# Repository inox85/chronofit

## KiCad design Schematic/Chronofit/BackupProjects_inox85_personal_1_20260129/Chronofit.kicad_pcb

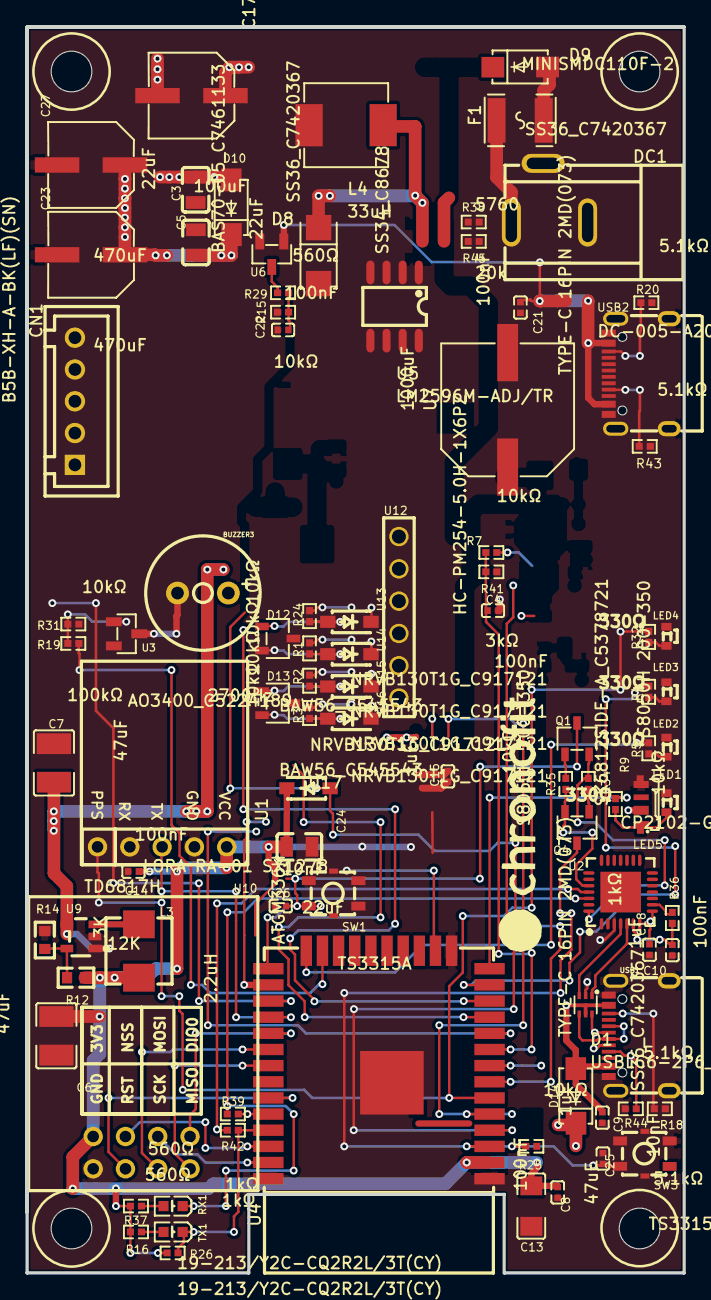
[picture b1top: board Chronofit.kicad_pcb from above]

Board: 4 copper layers, 51.7 x 98.0 mm, 96 parts (0 on the bottom side), 63 nets.

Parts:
BUZZER3: 2700Hz; BUZ-TH_BD9.0-P4.00-D0.6-FD
C3, C5, C24: 22uF; C0805
C4, C8, C14, C18, C21, C22: 100nF; C0402
C6, C7: 47uF; C1210
C9, C10, C15: 1uF; C0402
C13: 47uF; C1206
C17: 100uF; CAP-SMD_BD6.3-L6.6-W6.6-LS7.6-FD
C23, C27: 470uF; CAP-SMD_BD6.3-L6.6-W6.6-LS7.6-RD
C25, C26: 10nF; C0402
CN1: B5B-XH-A-BK(LF)(SN); CONN-TH_B5B-XH-A-BK-LF-SN
D1: USBLC6-2P6_C49451919; SOT-563_L1.6-W1.2-P0.50-LS1.6-BL
D8: SS34_C8678; SMA_L4.3-W2.6-LS5.2-RD
D9, D10, D14: SS36_C7420367; SMA_L4.3-W2.6-LS5.0-FD
D12, D13: BAW56_C545543; SOT-23-3_L2.9-W1.6-P1.90-LS2.8-BR
DC1: DC-005-A200; DC-IN-TH_DC-005-A200
F1: MINISMDC110F-2; F1812
Hole_gge181386: Hole_gge181386
Hole_gge189325: Hole_gge189325
Hole_gge196727: Hole_gge196727
Hole_gge200780: Hole_gge200780
L3: 2.2uH; IND-SMD_L5.2-W5.1
L4: 33uH; IND-SMD_L7.1-W6.6
LED1: BLUE_LED; LED-SMD_L1.7-W1.1-R-RD_GREEN
LED2: RED_LED; LED-SMD_L1.7-W1.1-R-RD_GREEN
LED3: GREEN_LED; LED-SMD_L1.7-W1.1-R-RD_GREEN
LED4: ORANGE_LED; LED-SMD_L1.7-W1.1-R-RD_GREEN
LED5: SK6812SIDE-A_C5378721; LED-SMD_4P-L4.0-W1.6-L
Q1, Q4: S8050H 200-350; SOT-23-3_L2.9-W1.6-P1.90-LS2.8-BR
R1, R2, R3, R7, R19, R24, R25, R26, R29, R34, R35: 10kΩ; R0402
R4, R5, R9, R32: 330Ω; R0402
R12: 12K; R0603
R14: 3K; R0603
R15, R16, R37: 560Ω; R0402
R18, R20, R43, R44: 5.1kΩ; R0402
R31: 100kΩ; R0402
R36, R39, R42: 1kΩ; R0402
R38: 20k; R0402
R41: 3kΩ; R0402
R45: 5760; R0402
RX1: 19-213/Y2C-CQ2R2L/3T(CY); LED0603-R-RD
SW1, SW3: TS3315A; SW-SMD_4P-L3.4-W3.4-P2.00-LS4.0_TS3315A160GF
TX1: 19-213/Y2C-CQ2R2L/3T(CY); LED0603-R-RD
U1: ATGM336H
U2: CP2102-GMR; WQFN-28_L5.0-W5.0-P0.50-BL-EP3.2
U3: AO3400_C5224189; SOT-23-3_L2.9-W1.3-P0.95-LS2.4-BR
U4: ESP32-WROOM-32(8MB); WIFIM-SMD_39P-L25.5-W18.0-P1.27
U5: LM2596M-ADJ/TR; SOP-8_L4.9-W3.9-P1.27-LS6.0-BL
U6: BAS70-05_C7461133; SOT-23-3_L2.9-W1.3-P1.90-LS2.4-BR
U7: 1000uF; CAP-SMD_BD10.0-L10.3-W10.3-LS11.3-FD
U9: TD6817H; SOT-23-5_L2.9-W1.6-P0.95-LS2.8-BR
U10: LORA RA-01 SX1278
U12: HC-PM254-5.0H-1X6PZ; HDR-TH_HC-PM254-5.0H-1X6PZ
U13, U14, U15, U16, U17: NRVB130T1G_C917121; SOD-123_L2.7-W1.6-LS3.7-RD-1
USB1, USB2: TYPE-C 16PIN 2MD(073); USB-C-SMD_TYPE-C-6PIN-2MD-073

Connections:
+3V3: C6.2, C8.2, C13.1, C14.2, C24.2, L3.2, R1.2, R2.2, R3.2, R12.2, R16.1, R24.2, R25.2, R26.2, R37.1, U1.5, U4.2, U10.5, U17.1
+5V: BUZZER3.1, C5.2, C7.2, C15.2, C18.1, C21.2, C23.1, C27.1, CN1.1, D10.2, D14.2, LED5.2, R7.2, U2.7, U2.8, U6.1, U7.1, U9.1, U9.4, USB2.2, USB2.11
+5_EXT_BATT: C3.2, D10.1, L4.2, R38.2
+12V: C17.1, D9.2, U5.1, U6.2, U12.1
BATT_CHK: C4.2, R7.1, R41.2, U4.9
BUZZER: R19.2, U4.23
CE_SDA: U4.33, U10.2
CSN_SCL: U4.36, U10.6
D8_1: D8.1, L4.1, U5.2
D9_1: D9.1, F1.2
D+: D1.4, USB1.6, USB1.8
D+_OUT: D1.3, U2.4
D-: D1.6, USB1.5, USB1.7
D-_OUT: D1.1, U2.5
DC1_1: DC1.1, F1.1
DIO: U4.29, U10.8
DTR: Q1.2, R34.1, U2.28
EN: C25.2, Q4.3, R25.1, SW3.2, U4.3
GND: C3.1, C4.1, C5.1, C6.1, C7.1, C8.1, C9.1, C10.1, C13.2, C14.1, C15.1, C17.2, C18.2, C21.1, C22.1, C23.2, C24.1, C25.1, C26.1, C27.2, CN1.5, D1.2, D8.2, D12.3, D13.3, DC1.2, LED1.2, LED2.2, LED3.2, LED4.2, LED5.4, R14.1, R15.1, R18.1, R20.2, R31.1, R41.1, R43.2, R44.1, R45.1, SW1.3, SW1.4, SW1.5, SW3.3, SW3.4, SW3.5, U1.4, U2.3, U3.2, U4.1, U4.15, U4.38, U4.39, U5.3, U5.5, U7.2, U9.2, U10.1, U12.6, USB1.1, USB1.12, USB1.13, USB1.14, USB2.1, USB2.12, USB2.13, USB2.14
GPIO0: C26.2, D13.2, Q1.3, R3.1, SW1.2, U4.16, U4.25, U16.2
IN1: D12.1, R24.1, U4.11, U13.2
IN2: D12.2, R1.1, U4.12, U14.2
IN3: D13.1, R2.1, U4.10, U15.2
L3_1: L3.1, U9.3
LED1: R9.2, U4.14
LED2: R5.2, U4.24
LED2_1: LED2.1, R5.1
LED3: R4.2, U4.13
LED3_1: LED3.1, R4.1
LED4_1: LED4.1, R32.1
MISO: U4.31, U10.4
MOSI: U4.37, U10.7
POWER_CHK: C22.2, R15.2, R29.1, U4.4, U17.2
PPS_GPS: R32.2, U1.1, U4.6
Q1_1: Q1.1, R35.2
Q4_1: Q4.1, R34.2
R12_1: R12.1, R14.2, U9.5
R29_2: R29.2, U6.3
R38_1: R38.1, R45.2, U5.4
RGB_LED: LED1.1, LED5.1, R9.1
RTS: Q4.2, R35.1, U2.24
RX0: R39.1, U4.34
RX1_1: R37.2, RX1.1
RX1_2: R39.2, RX1.2, U2.26
RX_GPS: U1.3, U4.28
SCK: U4.30, U10.3
TX0: R26.1, R42.1, TX1.2, U4.35
TX1_1: R16.2, TX1.1
TX_PRINTER: CN1.4, U4.27
U2_6: C10.2, R36.1, U2.6
U2_9: R36.2, U2.9
U2_25: R42.2, U2.25
U3_1: R19.1, R31.2, U3.1
U3_3: BUZZER3.2, U3.3
U12_2: U12.2, U13.1
U12_3: U12.3, U14.1
U12_4: U12.4, U15.1
U12_5: U12.5, U16.1
USB1_4: R44.2, USB1.4
USB1_10: R18.2, USB1.10
USB2_4: R43.1, USB2.4
USB2_10: R20.1, USB2.10
VBUS: C9.2, D1.5, D14.1, USB1.2, USB1.11

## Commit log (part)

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2026-01-02 Creazione nuovo progetto pulito
2026-01-03 Varie implementazioni
2026-01-03 Risoluzione problemi di sincro
2026-01-04 Revert "Risoluzione problemi di sincro"
    This reverts commit 822fe9ed9b7b362585123e8bc8ef85d785ed9c43.
2026-01-04 Applicato riferimento temporale epoch
2026-01-04 Aparentemente risolti problemi di sicronizzazione
2026-01-04 Apparentemente risolti problemidi sincronizzazione
2026-01-04 Aggiunta colonna Delta Time
2026-01-04 Modifiche per intertempi editRow
2026-01-04 Prima versione stabile a livello di sync
2026-01-06 Corretto bug overflow in checkpoint simulato
2026-01-06 Aggiunta visibilità colonne selezionabile
2026-01-06 Inizio implementazione compensazione quarzo in temperatura
2026-01-06 Inizio implementazione compensazione in temperatura
2026-01-07 Messa in sospeso compensazione in temperatura
2026-01-08 Customizzazione colonne tabella
2026-01-08 Aggiunta animazione inserimento righe tabella
2026-01-09 Aggiunta colonna elapsed
2026-01-09 Ottimizzazione tipi di messaggi ws
2026-01-09 Corretto editing riga, inizio implementazione broadcast modifica e corretto celle da modificare in modo robusto
2026-01-09 Corretto bug detecting powersource
2026-01-10 Economizzata dimensione json in filesystem
2026-01-13 Inizio introduzione modalità elapsed
2026-01-14 Corretto bug recupero sessione
2026-01-14 Aggiunti modelli 3d
2026-01-14 Inclusa libreria ArduiniJson in routes
2026-01-14 Completata modalità elapsed time
2026-01-15 Aggiornato editing row dopo risparmio memoria
2026-01-16 Aumentato tempo permanenza popup calibrazione
2026-01-16 Messo default unckecked su visualizzazione elapsed time
2026-01-16 Inizio sviluppo funzione penalità
2026-01-18 Finalizzata gestione delle penalità numeriche
2026-01-20 Aggiunte meccaniche e etichetta
2026-01-20 Aggiunte etichette
2026-01-20 Aggiunta gestione led per check client connessi
2026-01-20 Migliorata gestione elapsed mode con righe colorate e assegnati LEDs
2026-01-21 Aggiunta schermata di visualizzazione
2026-01-22 Aggiunta etichetta
2026-01-23 Aggiornata meccanica
2026-01-23 Eliminazione file meccanica vecchio
2026-01-23 Aggiunta schermata view
2026-01-25 Aggiunta stampa asincrona non bloccante
2026-01-25 Inserita nuovamente API time
2026-01-25 Sostiutiti simboli sottoscrizione
2026-01-28 Esportazioni tabelle potenziate
2026-01-28 Piccole modifiche web
2026-01-28 Spostato bottone clear session
2026-01-30 Prima implementazione non testata
2026-01-31 Portata avanti connessione a internet
2026-01-31 Quasi completata connessione ad internet
2026-02-01 Migliorata interfaccia connessione Internet
2026-02-01 Prima versione stabile di invio via eMail
2026-02-01 Arrivati al punto di doveri inserire la mail del destinatario
2026-02-02 Inserimento mail custom
2026-02-03 Aggiunto progetto scheda
2026-02-03 Assegnati led di segnalazione
2026-02-04 Reso asincrono il task di invio mail
2026-02-05 Corretti cursori
2026-02-05 Disabilitata conferma email
2026-02-06 Aggiunta ultima revisione coperchio
2026-02-09 Cambio suoni in parlato
2026-02-10 Aggiunto controllo su numero di righe tabella per mandare email
2026-02-10 fixato bug non refresh penality
2026-02-10 Sistemati suoni
2026-02-11 Correzione led sync request
2026-02-11 Correzione stato segnalazione GPS NavBar
2026-02-13 Tentativo di risoluzione problema test
2026-02-25 Iniziato sviluppo updater
2026-02-25 Corretto ordine dei sensori e bug sincronizzazione
2026-02-25 Aggiunto test DS3231
2026-02-26 Creato codice per RTC esterno
2026-02-26 Spostate releases
2026-02-26 Prima versione con sincronizzazione RTC funzionante
2026-02-26 Prima versione funzionante RTC
2026-02-27 Cambio modalità gestione resync
2026-02-27 Tentativi di utilizzo RTC ma con errori
2026-02-27 Configurazione GPS One shot
2026-03-02 Implementazione controllo drift
2026-03-02 Implementato disciplned
2026-03-03 Introdotto fattore di aging
2026-03-04 Proseguito con l'implementazione RTC controllato
2026-03-04 Implementazione pid per ottimizzazione aging
2026-03-04 Prova correzione verso
2026-03-05 Localizzato forse problema jitter
2026-03-05 Ripristinata calibrazione aging per vedere se funziona
2026-03-07 Prima versione di compensazione funzionante
2026-03-07 Aggiunta lettura temperatura
2026-03-08 Piccola pulizia codice
2026-03-09 Aumentata scelta dei tempi di resync
2026-03-09 Finalizzato controllo drift, aggiunta gestione aging, riformato sync test
2026-03-09 Aggiunti ignore
2026-03-09 Aggiunta impostazione agingFactor da web
2026-03-09 Pulizia route di calibrazione base dei tempi
2026-03-10 Coonvertiti identificativi linea in stringa
2026-03-11 Aggiunta gestione RTCTrigger anche a line sync
2026-03-11 Rimosso OTA per aumentare spazio
2026-03-14 Modifiche Pagina web
2026-03-14 Aggiunta possibilità di creare fs.bin
2026-03-17 Versione semi-stabile
2026-03-17 Aggiunta opzione mailgun
2026-03-18 Implementata mail SMTP
2026-03-18 Modifiche a updater
2026-03-18 Aggiunta segnalazione stato connessione wifi
2026-03-18 Recupero modifiche updater
2026-03-18 Miglioramento updater
2026-03-18 Modifiche non sostanziali
2026-03-19 Modifiche inconsistenti
2026-03-19 Miodifiche incosnsistenti
2026-03-22 Prima versione con rilascio in Merge + FS
2026-03-22 Corretta variabile uint32_t nel checkpoint manuale da webgui
2026-03-22 Rimossa gestione agingFactor in memoria non volatile
2026-03-22 Gestita impossibilità di accesso alla cartella updateFiles
2026-03-23 Iniziata implementazione programmazione separata
2026-03-23 Aggiunti dettagli in sistemSettungs e possibilità di scaricare files
2026-03-23 Ignorata cartella bin
2026-03-23 Corretti ignore
2026-03-24 Fix mail
2026-03-24 Gestita pagina view
2026-03-25 Definita per bene pagina view.html
2026-03-25 Iniziata lieve ottimizzazione RAM
2026-03-26 Ulteriori modifiche a invio mail
2026-03-27 Sistemato salvataggio aging che erra da fixare
2026-03-27 Aggiunta funzione per programmazione selettiva
2026-03-28 Tentetivo di limare bug su sync più o meno un secondo
2026-03-29 Inserita opzione One-shot sync
2026-03-31 Versione con stima del drift funzionante
2026-03-31 Arrotondamento dei millisecondi invece di trocamento
2026-04-01 Sistemato errori grafici
2026-04-01 Modifiche non strutturali
2026-04-01 Corretto rollover drift us
2026-04-01 Tentativo di gestire mancata connessione websocket
2026-04-01 Ulteriori miglioramenti al Sync Test
2026-04-03 Versione stabile per inizio sviluppo per nuovo HW
2026-04-04 Aggiunta possibilità di controllare led RGB e riformati PINs
2026-04-04 Modifiche non rilevanti
2026-04-05 Corretto pin I2C
2026-04-05 Rimosso metodo non utilizzato
2026-04-05 Aggiunto file di configurazione Claude
2026-04-05 Prova script principale migliorato
2026-04-07 Modifiche a chiusura prima del passagio a nuova revisione
2026-04-12 Introdotto split di versione
2026-04-14 RTC, WIFI LED, e PPS LED funzionanti
2026-04-14 Gestione led e risolto bug test Sync
2026-04-16 Corretta stringa di stampa e aggiunta partizione Custom
2026-04-16 Corretta stringa di stampa
2026-04-16 Inizio gestione LED Traffico
2026-04-17 Aggiunta segnalazione su routes
2026-04-18 Introduzione strumenti per versione 16MB
2026-04-18 Inizio introduzione strumenti per versione 16MB
2026-04-18 Aggiunto contollo presenza PPS per validare il FIX
2026-04-19 Aggiunta gps dettagliato
2026-04-19 Prova di connessione WiFi continua
2026-04-19 Snellite info GPS
2026-04-19 Milgioramento connessione WIFI
2026-04-19 Aggiunti delete e update per i files
2026-04-20 Disabilitata card checksum error pagina web gps.html
2026-04-20 Prova ottimizzazione stringhe NMEA per evitare errori
2026-04-20 Modifiche interfaccia gps diagnostics
2026-04-21 Prova implementazione sincronizzazione
2026-04-21 Aggiornato tutto per OTA
    Aggiornato
2026-04-21 Aggiunto aggiornamento filesystem
2026-04-21 Modifica numero decimali
2026-04-21 Ritrovata situazione stabile jitter NMEA
2026-04-22 Applicata combox per time precision
2026-04-22 Versione correttamente funzionante
2026-04-22 Gestione dei coockies
2026-04-22 Apparentemente/definitivamente risolto problema sincro
2026-04-23 Sistemata condizione di controllo per abilitazione sync-test
2026-04-23 Sistemato CientCaptive
2026-04-23 Risolto problema di sync-test mancati
2026-04-23 Aggiunto about, manuale e disconnect tool fix
2026-04-24 Aggiunto scritp fix al js
2026-04-24 Aggiunta prova MQTT
2026-04-24 Warning fixes e introduzione mqtt
2026-04-24 Risolto bug general popup message
2026-04-24 Migliorato sync
2026-04-25 Migliorato ma ancora problemi di connessione MQTT
2026-04-25 Consentita password vuota WiFi
2026-04-27 Introduzione splash custom e loading
2026-04-27 Miglioramento connessione WiFi
2026-04-27 Revert "Miglioramento connessione WiFi"
    This reverts commit ed35fd178ff83dd38b160bc8f0116d1b0f9123af.
2026-04-27 Modifiche mqtt
2026-04-28 Sistemati tentativi wifi
2026-04-28 Prima fase introduzione MQTT
2026-04-29 Riportato a condizione funzionante
2026-04-29 Rimozione MQTT, fix WiFi, ottimizzazioni frontend
2026-04-29 Riallineata versione funzionante
2026-04-29 Versione revisionata da Claude
2026-04-29 Doppio logo
2026-04-29 Doppio logo CSS
2026-04-29 File Claude
2026-04-30 aumentato numero di costruttori
2026-04-30 Aggiunta compressione files
2026-05-02 Ignorati files claude
2026-05-02 Introduzione mqtt via pubsub
2026-05-02 Prova con segnalazione DNS Fallito
2026-05-02 Gestione connessioni multiple wifi gestite
2026-05-03 Consolidati retries WiFi e connessione/disconnessione MQTT
2026-05-03 Aggiunti popup messaggi MQTT
2026-05-03 Prima fase MQTT conclusa
2026-05-04 Prova di spostamento mqtt su core 1 e aumentato watchdog
2026-05-04 Aumentato tempo watchdog
2026-05-04 disattivato dns e on notfound
2026-05-04 Rimesso dati access point di default
2026-05-04 Sostituita Icona
2026-05-04 Aggiunti files a compressione
2026-05-05 Aggiunte opzioni popup MQTT
2026-05-05 Gestione completa messaggi MQTT con popup e conferme
2026-05-05 Gestione messaggi mqtt con client disconnesso
2026-05-05 Reset git ignore
2026-05-05 Revert "Reset git ignore"
    This reverts commit fb1c45427bb2199cfec92cdf445b13436cef6fe1.
2026-05-05 Aggiunto chronofit 3.0
2026-05-05 Milglioramenti gestione messaggi MQTT
2026-05-06 Migliorata gestione MQTT
2026-05-06 Eliminato progetto di appoggio
2026-05-06 Aggiunta possibilità di ri-invio messaggi MQTT
2026-05-06 Ritoccato form WiFi
2026-05-10 Aggiornamento etichetta
2026-05-10 Risolto bug row rditing
2026-05-10 Inizio introduzione inibizione linea
2026-05-10 Gestione righe disabilitate
2026-05-10 Aggiunto reset competitor ad aggiunta linea
2026-05-11 Aggiunto numero client connessi
2026-05-11 Aggiunto MqttMonitor
2026-05-11 Aggiunta possibilità di caricare anagrafica competitors
2026-05-11 Ottimizzazione + reverse linee
2026-05-12 Aggiunta acquisizione competitor in .csv
2026-05-12 Aggiunta pagina di stream
2026-05-12 Aggiunta pagina broadcast overlay
2026-05-12 Prima bozza di schermate grafiche
2026-05-13 Aggiunte funzionalità tabella a tutte le views
2026-05-13 Aggiunte impostazioni overlay
2026-05-13 Aggiunti tools a progetto updater
2026-05-14 Migliorato MQTTmonitor
2026-05-14 Aggiunte password e sicurezze
2026-05-15 Migliorata GUI Mqtt Monitor
2026-05-15 Aggiunta customizzazione topic prefix
2026-05-15 Aggiunte impostazioni broker
2026-05-15 Aumentate funzioni tabella
2026-05-15 Provato a correggere PWA
2026-05-15 Aggiunto documento sulle API
2026-05-15 Tentato di correggere collasso impostazioni righe che non funzionano u mobile
2026-05-15 Tentativo fix definitivo collasso settings colonne
2026-05-16 Implementata API per checpointsFields
2026-05-17 Applicate misure di risparmio ram e bugfix opzioni tabella
2026-05-18 Correzione file APIs
2026-05-19 Modifiche GUI MqttMonitor
2026-05-19 Aggiunto debug seriale GPS disattivabile
2026-05-20 Aggiunta gestione lingue
2026-05-20 Aggiunti preset discipline
2026-05-20 Prima modifiche verso GUI dinamica
2026-05-21 Prima inplementazione GUI nuove
2026-05-21 Portata avanti nuova GUI
2026-05-22 Quasi terminato sviluppo nuova GUI
2026-05-23 Aggiunta opzione di mantenere inserimento competitor attivo
2026-05-23 Risolti problemi MQTT
2026-05-24 Prima versione che sembra funzionante
